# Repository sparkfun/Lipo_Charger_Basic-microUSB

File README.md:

SparkFun LiPo Charger Basic - Micro-USB
========================================

[*SparkFun LiPo Charger Basic - Micro-USB (PRT-10217)*](https://www.sparkfun.com/products/10217)

The SparkFun LiPo Charger Basic is stripped down of all features and just does one thing well - charge 3.7V LiPo cells at a rate of 500mA. 
It is designed to charge single-cell Li-Ion or Li-Polymer batteries. 
The board incorporates a charging circuit, status LED, connector for your battery (JST-type used in the batteries we carry), and a micro-USB connector. 
A small mounting hole allows this charger to be easily embedded into a project.

Repository Contents
-------------------
* **/Hardware** - Eagle design files (.brd, .sch)
* **/Production** - Production panel files (.brd)

Documentation
--------------
* **[SparkFun Fritzing repo](https://github.com/sparkfun/Fritzing_Parts)** - Fritzing diagrams for SparkFun products.
* **[SparkFun 3D Model repo](https://github.com/sparkfun/3D_Models)** - 3D models of SparkFun products. 

License Information
-------------------
This product is _**open source**_! 

The **hardware** is released under [Creative Commons ShareAlike 4.0 International](https://creativecommons.org/licenses/by-sa/4.0/).

Please use, reuse, and modify these files as you see fit. Please maintain attribution to SparkFun Electronics and release anything derivative under the same license.

Distributed as-is; no warranty is given.

- Your friends at SparkFun.

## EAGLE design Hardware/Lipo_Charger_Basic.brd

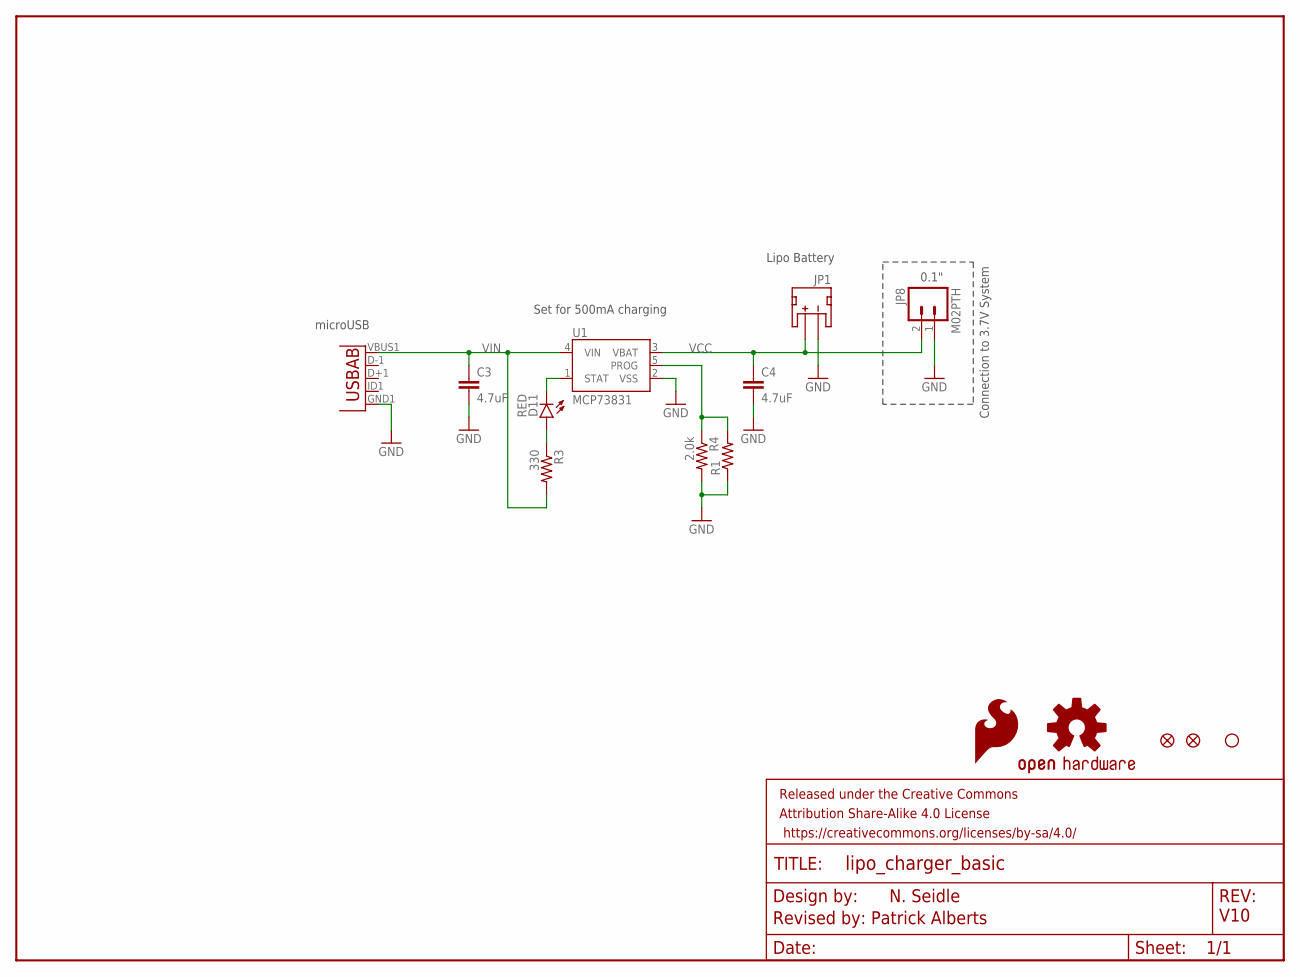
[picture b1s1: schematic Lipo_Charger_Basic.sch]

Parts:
C3, C4: 4.7uF; 0603-CAP
D11: RED; LED-0603
FRAME1: FRAME-LETTER; CREATIVE_COMMONS
JP1: JST; JST-2-SMD
JP2: STAND-OFF
JP3, JP4: FIDUCIAL1X2; FIDUCIAL-1X2
JP8: M02PTH; 1X02
JP9: Micro USB; USB-AB-MICRO-SMD_V03
LOGO1: OSHW-LOGOS; OSHW-LOGO-S
LOGO2: SFE_LOGO_FLAME.1_INCH; SFE_LOGO_FLAME_.1
R1: RESISTORPTH-1/4W-VERT-KIT; AXIAL-0.1EZ
R3: 330; 0603-RES
R4: 2.0k; 0603-RES
U1: MCP73831; SOT23-5

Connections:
GND: C3.2, C4.2, JP1.1 (-), JP8.1, JP9.GND1 (GND), R1.P$1 (1), R4.2, U1.2 (VSS)
unnamed: D11.A, R3.1
PROG: R1.P$2 (2), R4.1, U1.5 (PROG)
STAT: D11.C, U1.1 (STAT)
VCC: C4.1, JP1.2 (+), JP8.2, U1.3 (VBAT)
VIN: C3.1, JP9.VBUS1 (VBUS), R3.2, U1.4 (VIN)

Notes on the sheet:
Set for 500mA charging
Connection to 3.7V System
0.1"
N. Seidle
microUSB
Revised by: Patrick Alberts
V10
Lipo Battery

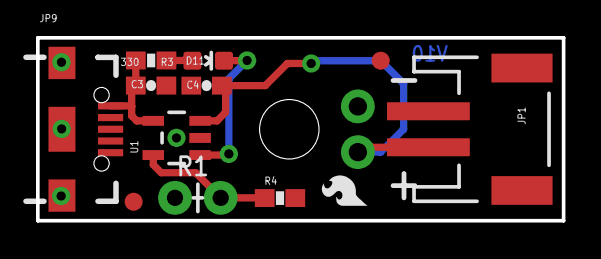
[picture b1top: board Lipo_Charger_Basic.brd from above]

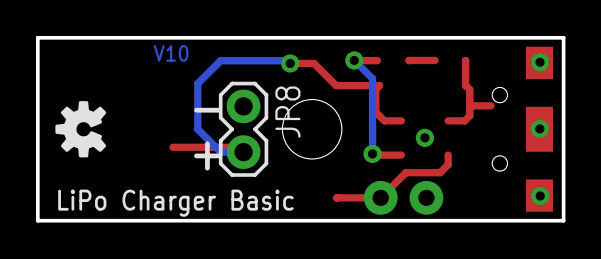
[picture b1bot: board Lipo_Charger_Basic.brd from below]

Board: 2 copper layers, 29.2 x 10.2 mm, 16 parts (2 on the bottom side), 6 nets.

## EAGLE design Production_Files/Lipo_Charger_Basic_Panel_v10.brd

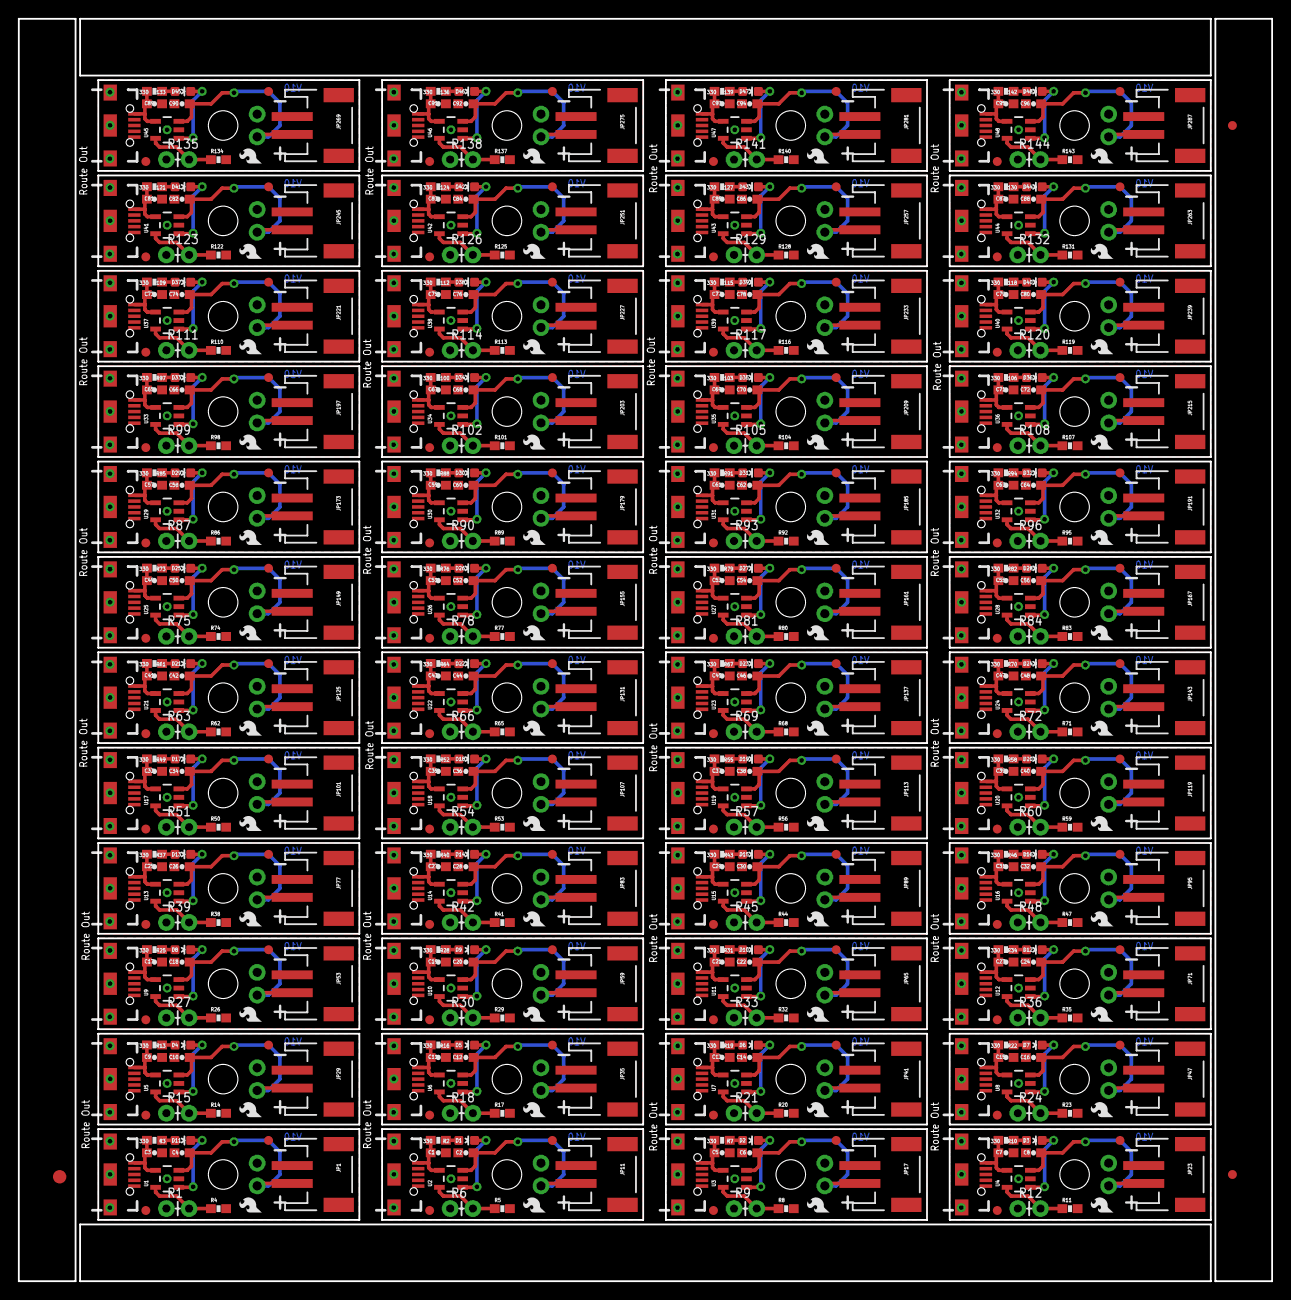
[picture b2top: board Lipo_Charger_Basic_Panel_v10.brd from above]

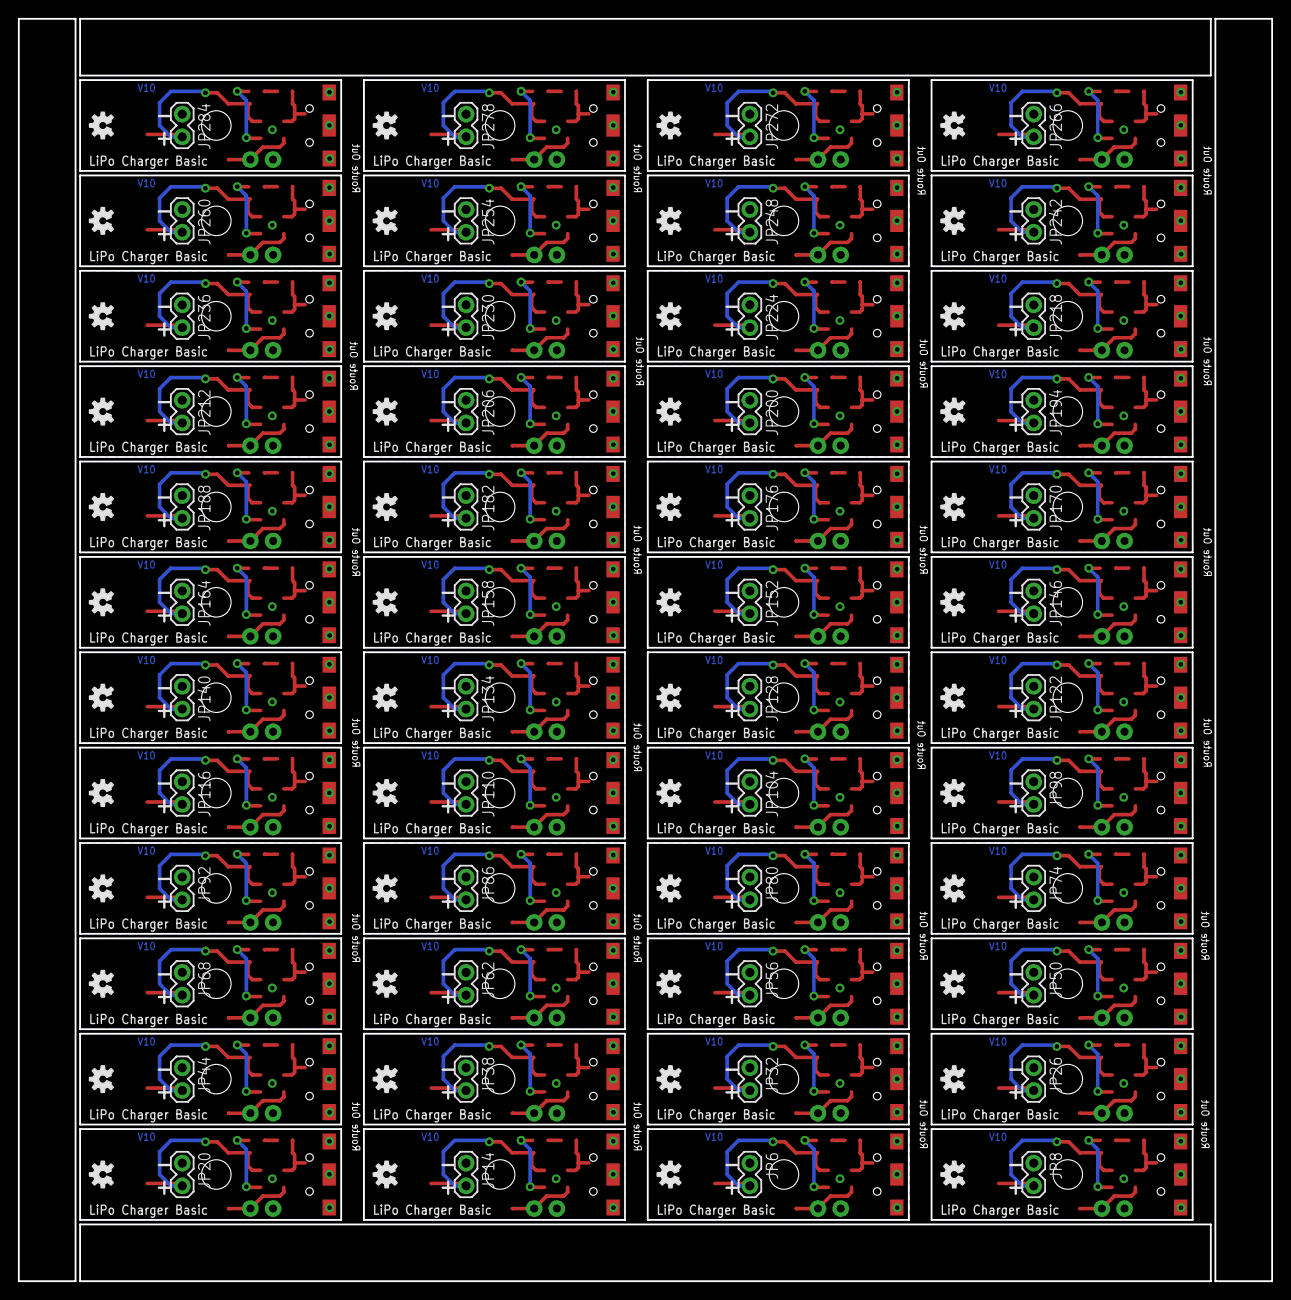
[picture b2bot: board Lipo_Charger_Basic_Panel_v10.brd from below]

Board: 2 copper layers, 140.2 x 141.2 mm, 723 parts (96 on the bottom side), 288 nets.

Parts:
C1, C2, C3, C4, C5, C6, C7, C8, C9, C10, C11, C12, C13, C14, C15, C16, C17, C18, C19, C20, C21, C22, C23, C24, C25, C26, C27, C28, C29, C30, C31, C32, C33, C34, C35, C36, C37, C38, C39, C40, C41, C42, C43, C44, C45, C46, C47, C48, C49, C50, C51, C52, C53, C54, C55, C56, C57, C58, C59, C60, C61, C62, C63, C64, C65, C66, C67, C68, C69, C70, C71, C72, C73, C74, C75, C76, C77, C78, C79, C80, C81, C82, C83, C84, C85, C86, C87, C88, C89, C90, C91, C92, C93, C94, C95, C96: 4.7uF; 0603-CAP
D1, D2, D3, D4, D5, D6, D7, D8, D9, D10, D11, D12, D13, D14, D15, D16, D17, D18, D19, D20, D21, D22, D23, D24, D25, D26, D27, D28, D29, D30, D31, D32, D33, D34, D35, D36, D37, D38, D39, D40, D41, D42, D43, D44, D45, D46, D47, D48: RED; LED-0603
E$1: FIDUCIAL-1.5X3
E$5, E$6: FIDUCIAL-1X2
JP1, JP11, JP17, JP23, JP29, JP35, JP41, JP47, JP53, JP59, JP65, JP71, JP77, JP83, JP89, JP95, JP101, JP107, JP113, JP119, JP125, JP131, JP137, JP143, JP149, JP155, JP161, JP167, JP173, JP179, JP185, JP191, JP197, JP203, JP209, JP215, JP221, JP227, JP233, JP239, JP245, JP251, JP257, JP263, JP269, JP275, JP281, JP287: JST; JST-2-SMD
JP2, JP5, JP13, JP19, JP25, JP31, JP37, JP43, JP49, JP55, JP61, JP67, JP73, JP79, JP85, JP91, JP97, JP103, JP109, JP115, JP121, JP127, JP133, JP139, JP145, JP151, JP157, JP163, JP169, JP175, JP181, JP187, JP193, JP199, JP205, JP211, JP217, JP223, JP229, JP235, JP241, JP247, JP253, JP259, JP265, JP271, JP277, JP283: STAND-OFF
JP3, JP4, JP10, JP12, JP16, JP18, JP22, JP24, JP28, JP30, JP34, JP36, JP40, JP42, JP46, JP48, JP52, JP54, JP58, JP60, JP64, JP66, JP70, JP72, JP76, JP78, JP82, JP84, JP88, JP90, JP94, JP96, JP100, JP102, JP106, JP108, JP112, JP114, JP118, JP120, JP124, JP126, JP130, JP132, JP136, JP138, JP142, JP144, JP148, JP150, JP154, JP156, JP160, JP162, JP166, JP168, JP172, JP174, JP178, JP180, JP184, JP186, JP190, JP192, JP196, JP198, JP202, JP204, JP208, JP210, JP214, JP216, JP220, JP222, JP226, JP228, JP232, JP234, JP238, JP240, JP244, JP246, JP250, JP252, JP256, JP258, JP262, JP264, JP268, JP270, JP274, JP276, JP280, JP282, JP286, JP288: FIDUCIAL1X2; FIDUCIAL-1X2
JP6, JP8, JP14, JP20, JP26, JP32, JP38, JP44, JP50, JP56, JP62, JP68, JP74, JP80, JP86, JP92, JP98, JP104, JP110, JP116, JP122, JP128, JP134, JP140, JP146, JP152, JP158, JP164, JP170, JP176, JP182, JP188, JP194, JP200, JP206, JP212, JP218, JP224, JP230, JP236, JP242, JP248, JP254, JP260, JP266, JP272, JP278, JP284: M02PTH; 1X02
JP7, JP9, JP15, JP21, JP27, JP33, JP39, JP45, JP51, JP57, JP63, JP69, JP75, JP81, JP87, JP93, JP99, JP105, JP111, JP117, JP123, JP129, JP135, JP141, JP147, JP153, JP159, JP165, JP171, JP177, JP183, JP189, JP195, JP201, JP207, JP213, JP219, JP225, JP231, JP237, JP243, JP249, JP255, JP261, JP267, JP273, JP279, JP285: Micro USB; USB-AB-MICRO-SMD_V03
LOGO1, LOGO3, LOGO5, LOGO7, LOGO9, LOGO11, LOGO13, LOGO15, LOGO17, LOGO19, LOGO21, LOGO23, LOGO25, LOGO27, LOGO29, LOGO31, LOGO33, LOGO35, LOGO37, LOGO39, LOGO41, LOGO43, LOGO45, LOGO47, LOGO49, LOGO51, LOGO53, LOGO55, LOGO57, LOGO59, LOGO61, LOGO63, LOGO65, LOGO67, LOGO69, LOGO71, LOGO73, LOGO75, LOGO77, LOGO79, LOGO81, LOGO83, LOGO85, LOGO87, LOGO89, LOGO91, LOGO93, LOGO95: OSHW-LOGOS; OSHW-LOGO-S
LOGO2, LOGO4, LOGO6, LOGO8, LOGO10, LOGO12, LOGO14, LOGO16, LOGO18, LOGO20, LOGO22, LOGO24, LOGO26, LOGO28, LOGO30, LOGO32, LOGO34, LOGO36, LOGO38, LOGO40, LOGO42, LOGO44, LOGO46, LOGO48, LOGO50, LOGO52, LOGO54, LOGO56, LOGO58, LOGO60, LOGO62, LOGO64, LOGO66, LOGO68, LOGO70, LOGO72, LOGO74, LOGO76, LOGO78, LOGO80, LOGO82, LOGO84, LOGO86, LOGO88, LOGO90, LOGO92, LOGO94, LOGO96: SFE_LOGO_FLAME.1_INCH; SFE_LOGO_FLAME_.1
R1, R6, R9, R12, R15, R18, R21, R24, R27, R30, R33, R36, R39, R42, R45, R48, R51, R54, R57, R60, R63, R66, R69, R72, R75, R78, R81, R84, R87, R90, R93, R96, R99, R102, R105, R108, R111, R114, R117, R120, R123, R126, R129, R132, R135, R138, R141, R144: AXIAL-0.1EZ
R2, R3, R7, R10, R13, R16, R19, R22, R25, R28, R31, R34, R37, R40, R43, R46, R49, R52, R55, R58, R61, R64, R67, R70, R73, R76, R79, R82, R85, R88, R91, R94, R97, R100, R103, R106, R109, R112, R115, R118, R121, R124, R127, R130, R133, R136, R139, R142: 330; 0603-RES
R4, R5, R8, R11, R14, R17, R20, R23, R26, R29, R32, R35, R38, R41, R44, R47, R50, R53, R56, R59, R62, R65, R68, R71, R74, R77, R80, R83, R86, R89, R92, R95, R98, R101, R104, R107, R110, R113, R116, R119, R122, R125, R128, R131, R134, R137, R140, R143: 2.0k; 0603-RES
U1, U2, U3, U4, U5, U6, U7, U8, U9, U10, U11, U12, U13, U14, U15, U16, U17, U18, U19, U20, U21, U22, U23, U24, U25, U26, U27, U28, U29, U30, U31, U32, U33, U34, U35, U36, U37, U38, U39, U40, U41, U42, U43, U44, U45, U46, U47, U48: MCP73831; SOT23-5

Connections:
GND: C3.2, C4.2, JP1.1, JP8.1, JP9.GND1, R1.P$1, R4.2, U1.2
GND1: C1.2, C2.2, JP6.1, JP7.GND1, JP11.1, R5.2, R6.P$1, U2.2
GND2: C5.2, C6.2, JP14.1, JP15.GND1, JP17.1, R8.2, R9.P$1, U3.2
GND3: C7.2, C8.2, JP20.1, JP21.GND1, JP23.1, R11.2, R12.P$1, U4.2
GND4: C9.2, C10.2, JP26.1, JP27.GND1, JP29.1, R14.2, R15.P$1, U5.2
GND5: C11.2, C12.2, JP32.1, JP33.GND1, JP35.1, R17.2, R18.P$1, U6.2
GND6: C13.2, C14.2, JP38.1, JP39.GND1, JP41.1, R20.2, R21.P$1, U7.2
GND7: C15.2, C16.2, JP44.1, JP45.GND1, JP47.1, R23.2, R24.P$1, U8.2
GND8: C17.2, C18.2, JP50.1, JP51.GND1, JP53.1, R26.2, R27.P$1, U9.2
GND9: C19.2, C20.2, JP56.1, JP57.GND1, JP59.1, R29.2, R30.P$1, U10.2
GND10: C21.2, C22.2, JP62.1, JP63.GND1, JP65.1, R32.2, R33.P$1, U11.2
GND11: C23.2, C24.2, JP68.1, JP69.GND1, JP71.1, R35.2, R36.P$1, U12.2
GND12: C25.2, C26.2, JP74.1, JP75.GND1, JP77.1, R38.2, R39.P$1, U13.2
GND13: C27.2, C28.2, JP80.1, JP81.GND1, JP83.1, R41.2, R42.P$1, U14.2
GND14: C29.2, C30.2, JP86.1, JP87.GND1, JP89.1, R44.2, R45.P$1, U15.2
GND15: C31.2, C32.2, JP92.1, JP93.GND1, JP95.1, R47.2, R48.P$1, U16.2
GND16: C33.2, C34.2, JP98.1, JP99.GND1, JP101.1, R50.2, R51.P$1, U17.2
GND17: C35.2, C36.2, JP104.1, JP105.GND1, JP107.1, R53.2, R54.P$1, U18.2
GND18: C37.2, C38.2, JP110.1, JP111.GND1, JP113.1, R56.2, R57.P$1, U19.2
GND19: C39.2, C40.2, JP116.1, JP117.GND1, JP119.1, R59.2, R60.P$1, U20.2
GND20: C41.2, C42.2, JP122.1, JP123.GND1, JP125.1, R62.2, R63.P$1, U21.2
GND21: C43.2, C44.2, JP128.1, JP129.GND1, JP131.1, R65.2, R66.P$1, U22.2
GND22: C45.2, C46.2, JP134.1, JP135.GND1, JP137.1, R68.2, R69.P$1, U23.2
GND23: C47.2, C48.2, JP140.1, JP141.GND1, JP143.1, R71.2, R72.P$1, U24.2
GND24: C49.2, C50.2, JP146.1, JP147.GND1, JP149.1, R74.2, R75.P$1, U25.2
GND25: C51.2, C52.2, JP152.1, JP153.GND1, JP155.1, R77.2, R78.P$1, U26.2
GND26: C53.2, C54.2, JP158.1, JP159.GND1, JP161.1, R80.2, R81.P$1, U27.2
GND27: C55.2, C56.2, JP164.1, JP165.GND1, JP167.1, R83.2, R84.P$1, U28.2
GND28: C57.2, C58.2, JP170.1, JP171.GND1, JP173.1, R86.2, R87.P$1, U29.2
GND29: C59.2, C60.2, JP176.1, JP177.GND1, JP179.1, R89.2, R90.P$1, U30.2
GND30: C61.2, C62.2, JP182.1, JP183.GND1, JP185.1, R92.2, R93.P$1, U31.2
GND31: C63.2, C64.2, JP188.1, JP189.GND1, JP191.1, R95.2, R96.P$1, U32.2
GND32: C65.2, C66.2, JP194.1, JP195.GND1, JP197.1, R98.2, R99.P$1, U33.2
GND33: C67.2, C68.2, JP200.1, JP201.GND1, JP203.1, R101.2, R102.P$1, U34.2
GND34: C69.2, C70.2, JP206.1, JP207.GND1, JP209.1, R104.2, R105.P$1, U35.2
GND35: C71.2, C72.2, JP212.1, JP213.GND1, JP215.1, R107.2, R108.P$1, U36.2
GND36: C73.2, C74.2, JP218.1, JP219.GND1, JP221.1, R110.2, R111.P$1, U37.2
GND37: C75.2, C76.2, JP224.1, JP225.GND1, JP227.1, R113.2, R114.P$1, U38.2
GND38: C77.2, C78.2, JP230.1, JP231.GND1, JP233.1, R116.2, R117.P$1, U39.2
GND39: C79.2, C80.2, JP236.1, JP237.GND1, JP239.1, R119.2, R120.P$1, U40.2
GND40: C81.2, C82.2, JP242.1, JP243.GND1, JP245.1, R122.2, R123.P$1, U41.2
GND41: C83.2, C84.2, JP248.1, JP249.GND1, JP251.1, R125.2, R126.P$1, U42.2
GND42: C85.2, C86.2, JP254.1, JP255.GND1, JP257.1, R128.2, R129.P$1, U43.2
GND43: C87.2, C88.2, JP260.1, JP261.GND1, JP263.1, R131.2, R132.P$1, U44.2
GND44: C89.2, C90.2, JP266.1, JP267.GND1, JP269.1, R134.2, R135.P$1, U45.2
GND45: C91.2, C92.2, JP272.1, JP273.GND1, JP275.1, R137.2, R138.P$1, U46.2
GND46: C93.2, C94.2, JP278.1, JP279.GND1, JP281.1, R140.2, R141.P$1, U47.2
GND47: C95.2, C96.2, JP284.1, JP285.GND1, JP287.1, R143.2, R144.P$1, U48.2
unnamed: D1.A, R2.1
unnamed: D2.A, R7.1
unnamed: D11.A, R3.1
unnamed: D3.A, R10.1
unnamed: D4.A, R13.1
unnamed: D5.A, R16.1
unnamed: D6.A, R19.1
unnamed: D7.A, R22.1
unnamed: D8.A, R25.1
unnamed: D9.A, R28.1
unnamed: D10.A, R31.1
unnamed: D12.A, R34.1
unnamed: D13.A, R37.1
unnamed: D14.A, R40.1
unnamed: D15.A, R43.1
unnamed: D16.A, R46.1
unnamed: D17.A, R49.1
unnamed: D18.A, R52.1
unnamed: D19.A, R55.1
unnamed: D20.A, R58.1
unnamed: D21.A, R61.1
unnamed: D22.A, R64.1
unnamed: D23.A, R67.1
unnamed: D24.A, R70.1
unnamed: D25.A, R73.1
unnamed: D26.A, R76.1
unnamed: D27.A, R79.1
unnamed: D28.A, R82.1
unnamed: D29.A, R85.1
unnamed: D30.A, R88.1
unnamed: D31.A, R91.1
unnamed: D32.A, R94.1
unnamed: D33.A, R97.1
unnamed: D34.A, R100.1
unnamed: D35.A, R103.1
unnamed: D36.A, R106.1
unnamed: D37.A, R109.1
unnamed: D38.A, R112.1
unnamed: D39.A, R115.1
unnamed: D40.A, R118.1
unnamed: D41.A, R121.1
unnamed: D42.A, R124.1
unnamed: D43.A, R127.1
unnamed: D44.A, R130.1
unnamed: D45.A, R133.1
unnamed: D46.A, R136.1
unnamed: D47.A, R139.1
unnamed: D48.A, R142.1
PROG: R1.P$2, R4.1, U1.5
PROG1: R5.1, R6.P$2, U2.5
PROG2: R8.1, R9.P$2, U3.5
PROG3: R11.1, R12.P$2, U4.5
PROG4: R14.1, R15.P$2, U5.5
PROG5: R17.1, R18.P$2, U6.5
PROG6: R20.1, R21.P$2, U7.5
PROG7: R23.1, R24.P$2, U8.5
PROG8: R26.1, R27.P$2, U9.5
PROG9: R29.1, R30.P$2, U10.5
PROG10: R32.1, R33.P$2, U11.5
PROG11: R35.1, R36.P$2, U12.5
PROG12: R38.1, R39.P$2, U13.5
PROG13: R41.1, R42.P$2, U14.5
PROG14: R44.1, R45.P$2, U15.5
PROG15: R47.1, R48.P$2, U16.5
PROG16: R50.1, R51.P$2, U17.5
PROG17: R53.1, R54.P$2, U18.5
PROG18: R56.1, R57.P$2, U19.5
PROG19: R59.1, R60.P$2, U20.5
PROG20: R62.1, R63.P$2, U21.5
PROG21: R65.1, R66.P$2, U22.5
PROG22: R68.1, R69.P$2, U23.5
PROG23: R71.1, R72.P$2, U24.5
PROG24: R74.1, R75.P$2, U25.5
PROG25: R77.1, R78.P$2, U26.5
PROG26: R80.1, R81.P$2, U27.5
PROG27: R83.1, R84.P$2, U28.5
PROG28: R86.1, R87.P$2, U29.5
PROG29: R89.1, R90.P$2, U30.5
PROG30: R92.1, R93.P$2, U31.5
PROG31: R95.1, R96.P$2, U32.5
PROG32: R98.1, R99.P$2, U33.5
PROG33: R101.1, R102.P$2, U34.5
PROG34: R104.1, R105.P$2, U35.5
PROG35: R107.1, R108.P$2, U36.5
PROG36: R110.1, R111.P$2, U37.5
PROG37: R113.1, R114.P$2, U38.5
PROG38: R116.1, R117.P$2, U39.5
PROG39: R119.1, R120.P$2, U40.5
PROG40: R122.1, R123.P$2, U41.5
PROG41: R125.1, R126.P$2, U42.5
PROG42: R128.1, R129.P$2, U43.5
PROG43: R131.1, R132.P$2, U44.5
PROG44: R134.1, R135.P$2, U45.5
PROG45: R137.1, R138.P$2, U46.5
PROG46: R140.1, R141.P$2, U47.5
PROG47: R143.1, R144.P$2, U48.5
STAT: D11.C, U1.1
STAT1: D1.C, U2.1
STAT2: D2.C, U3.1
STAT3: D3.C, U4.1
STAT4: D4.C, U5.1
STAT5: D5.C, U6.1
STAT6: D6.C, U7.1
STAT7: D7.C, U8.1
STAT8: D8.C, U9.1
STAT9: D9.C, U10.1
STAT10: D10.C, U11.1
STAT11: D12.C, U12.1
STAT12: D13.C, U13.1
STAT13: D14.C, U14.1
STAT14: D15.C, U15.1
STAT15: D16.C, U16.1
STAT16: D17.C, U17.1
STAT17: D18.C, U18.1
STAT18: D19.C, U19.1
STAT19: D20.C, U20.1
STAT20: D21.C, U21.1
STAT21: D22.C, U22.1
STAT22: D23.C, U23.1
STAT23: D24.C, U24.1
STAT24: D25.C, U25.1
STAT25: D26.C, U26.1
STAT26: D27.C, U27.1
STAT27: D28.C, U28.1
STAT28: D29.C, U29.1
STAT29: D30.C, U30.1
STAT30: D31.C, U31.1
STAT31: D32.C, U32.1
STAT32: D33.C, U33.1
STAT33: D34.C, U34.1
STAT34: D35.C, U35.1
STAT35: D36.C, U36.1
STAT36: D37.C, U37.1
STAT37: D38.C, U38.1
STAT38: D39.C, U39.1
STAT39: D40.C, U40.1
STAT40: D41.C, U41.1
STAT41: D42.C, U42.1
STAT42: D43.C, U43.1
STAT43: D44.C, U44.1
STAT44: D45.C, U45.1
STAT45: D46.C, U46.1
STAT46: D47.C, U47.1
STAT47: D48.C, U48.1
VCC: C4.1, JP1.2, JP8.2, U1.3
VCC1: C2.1, JP6.2, JP11.2, U2.3
VCC2: C6.1, JP14.2, JP17.2, U3.3
VCC3: C8.1, JP20.2, JP23.2, U4.3
VCC4: C10.1, JP26.2, JP29.2, U5.3
VCC5: C12.1, JP32.2, JP35.2, U6.3
VCC6: C14.1, JP38.2, JP41.2, U7.3
VCC7: C16.1, JP44.2, JP47.2, U8.3
VCC8: C18.1, JP50.2, JP53.2, U9.3
VCC9: C20.1, JP56.2, JP59.2, U10.3
VCC10: C22.1, JP62.2, JP65.2, U11.3
VCC11: C24.1, JP68.2, JP71.2, U12.3
VCC12: C26.1, JP74.2, JP77.2, U13.3
VCC13: C28.1, JP80.2, JP83.2, U14.3
VCC14: C30.1, JP86.2, JP89.2, U15.3
VCC15: C32.1, JP92.2, JP95.2, U16.3
VCC16: C34.1, JP98.2, JP101.2, U17.3
VCC17: C36.1, JP104.2, JP107.2, U18.3
VCC18: C38.1, JP110.2, JP113.2, U19.3
VCC19: C40.1, JP116.2, JP119.2, U20.3
VCC20: C42.1, JP122.2, JP125.2, U21.3
VCC21: C44.1, JP128.2, JP131.2, U22.3
VCC22: C46.1, JP134.2, JP137.2, U23.3
VCC23: C48.1, JP140.2, JP143.2, U24.3
VCC24: C50.1, JP146.2, JP149.2, U25.3
VCC25: C52.1, JP152.2, JP155.2, U26.3
VCC26: C54.1, JP158.2, JP161.2, U27.3
VCC27: C56.1, JP164.2, JP167.2, U28.3
VCC28: C58.1, JP170.2, JP173.2, U29.3
VCC29: C60.1, JP176.2, JP179.2, U30.3
VCC30: C62.1, JP182.2, JP185.2, U31.3
VCC31: C64.1, JP188.2, JP191.2, U32.3
VCC32: C66.1, JP194.2, JP197.2, U33.3
VCC33: C68.1, JP200.2, JP203.2, U34.3
VCC34: C70.1, JP206.2, JP209.2, U35.3
VCC35: C72.1, JP212.2, JP215.2, U36.3
VCC36: C74.1, JP218.2, JP221.2, U37.3
VCC37: C76.1, JP224.2, JP227.2, U38.3
VCC38: C78.1, JP230.2, JP233.2, U39.3
VCC39: C80.1, JP236.2, JP239.2, U40.3
VCC40: C82.1, JP242.2, JP245.2, U41.3
VCC41: C84.1, JP248.2, JP251.2, U42.3
VCC42: C86.1, JP254.2, JP257.2, U43.3
VCC43: C88.1, JP260.2, JP263.2, U44.3
VCC44: C90.1, JP266.2, JP269.2, U45.3
VCC45: C92.1, JP272.2, JP275.2, U46.3
VCC46: C94.1, JP278.2, JP281.2, U47.3
VCC47: C96.1, JP284.2, JP287.2, U48.3
VIN: C3.1, JP9.VBUS1, R3.2, U1.4
VIN1: C1.1, JP7.VBUS1, R2.2, U2.4
VIN2: C5.1, JP15.VBUS1, R7.2, U3.4
VIN3: C7.1, JP21.VBUS1, R10.2, U4.4
VIN4: C9.1, JP27.VBUS1, R13.2, U5.4
VIN5: C11.1, JP33.VBUS1, R16.2, U6.4
VIN6: C13.1, JP39.VBUS1, R19.2, U7.4
VIN7: C15.1, JP45.VBUS1, R22.2, U8.4
VIN8: C17.1, JP51.VBUS1, R25.2, U9.4
VIN9: C19.1, JP57.VBUS1, R28.2, U10.4
VIN10: C21.1, JP63.VBUS1, R31.2, U11.4
VIN11: C23.1, JP69.VBUS1, R34.2, U12.4
VIN12: C25.1, JP75.VBUS1, R37.2, U13.4
VIN13: C27.1, JP81.VBUS1, R40.2, U14.4
VIN14: C29.1, JP87.VBUS1, R43.2, U15.4
VIN15: C31.1, JP93.VBUS1, R46.2, U16.4
VIN16: C33.1, JP99.VBUS1, R49.2, U17.4
VIN17: C35.1, JP105.VBUS1, R52.2, U18.4
VIN18: C37.1, JP111.VBUS1, R55.2, U19.4
VIN19: C39.1, JP117.VBUS1, R58.2, U20.4
VIN20: C41.1, JP123.VBUS1, R61.2, U21.4
VIN21: C43.1, JP129.VBUS1, R64.2, U22.4
VIN22: C45.1, JP135.VBUS1, R67.2, U23.4
VIN23: C47.1, JP141.VBUS1, R70.2, U24.4
VIN24: C49.1, JP147.VBUS1, R73.2, U25.4
VIN25: C51.1, JP153.VBUS1, R76.2, U26.4
VIN26: C53.1, JP159.VBUS1, R79.2, U27.4
VIN27: C55.1, JP165.VBUS1, R82.2, U28.4
VIN28: C57.1, JP171.VBUS1, R85.2, U29.4
VIN29: C59.1, JP177.VBUS1, R88.2, U30.4
VIN30: C61.1, JP183.VBUS1, R91.2, U31.4
VIN31: C63.1, JP189.VBUS1, R94.2, U32.4
VIN32: C65.1, JP195.VBUS1, R97.2, U33.4
VIN33: C67.1, JP201.VBUS1, R100.2, U34.4
VIN34: C69.1, JP207.VBUS1, R103.2, U35.4
VIN35: C71.1, JP213.VBUS1, R106.2, U36.4
VIN36: C73.1, JP219.VBUS1, R109.2, U37.4
VIN37: C75.1, JP225.VBUS1, R112.2, U38.4
VIN38: C77.1, JP231.VBUS1, R115.2, U39.4
VIN39: C79.1, JP237.VBUS1, R118.2, U40.4
VIN40: C81.1, JP243.VBUS1, R121.2, U41.4
VIN41: C83.1, JP249.VBUS1, R124.2, U42.4
VIN42: C85.1, JP255.VBUS1, R127.2, U43.4
VIN43: C87.1, JP261.VBUS1, R130.2, U44.4
VIN44: C89.1, JP267.VBUS1, R133.2, U45.4
VIN45: C91.1, JP273.VBUS1, R136.2, U46.4
VIN46: C93.1, JP279.VBUS1, R139.2, U47.4
VIN47: C95.1, JP285.VBUS1, R142.2, U48.4

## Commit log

2014-10-28 Initial commit with brd/sch files
2014-10-28 Updated to 0603/Frame/Dimension change
    Updates all components to 0603
    Sch to Frame letter
    Added oshw logo
    minor re routing
    Updated microb to bossed version
2015-01-08 Fixed sch and moved micro B
2015-01-14 Computer Change update.
2015-01-26 qc checklist issues fixed.
2015-01-27 Fixed final qc checklist issues
2015-02-17 Fixed silk issue, changed rev #'s for reds
2015-03-06 qc cl items fixed
2015-03-06 created panel v10
2015-05-15 Updating directory structure, fixing README

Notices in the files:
parts and their libraries:
SparkFun-Resistors: Licensing: Creative Commons ShareAlike 4.0 International - https://creativecommons.org/licenses/by-sa/4.0
SparkFun-Aesthetics: Released under the Creative Commons Attribution Share-Alike 4.0 License
SparkFun-Aesthetics: Released under the Creative Commons
